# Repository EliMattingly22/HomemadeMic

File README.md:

# HomemadeMic
A simple homemade studio microphone

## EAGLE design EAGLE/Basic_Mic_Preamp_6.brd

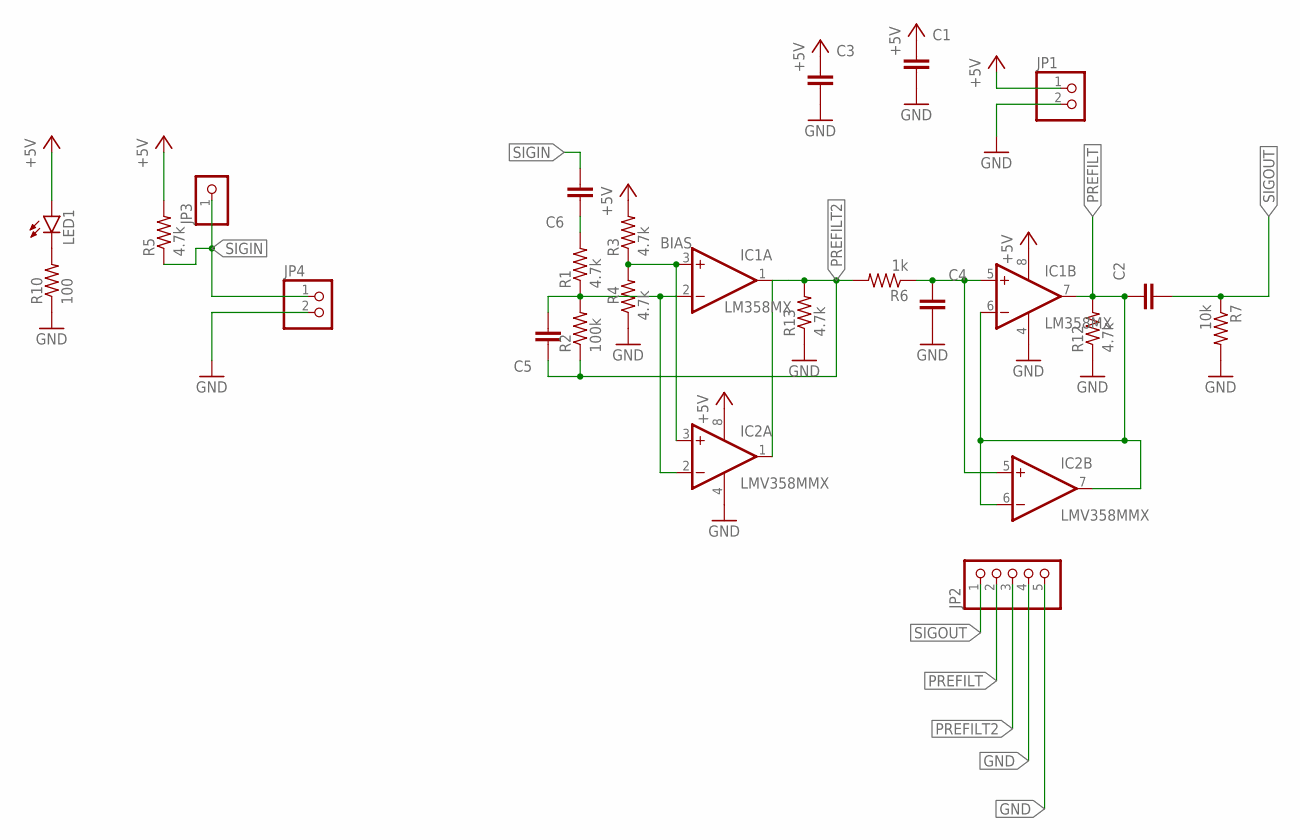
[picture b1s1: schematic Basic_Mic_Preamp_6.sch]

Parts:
C1: 10u; C1206K
C2, C6: 1u; C1206K
C3, C4: .01u; C1206K
C5: 500p; C1206K
IC1: LM358MX; SO08
IC2: LMV358MMX; MSOP08
JP1, JP4: PINHD-1X2/90; 1X02/90
JP2: PINHD-1X5/90; 1X05/90
JP3: PINHD-1X1; 1X01
LED1: LEDCHIPLED_1206; CHIPLED_1206
R1, R3, R4, R5, R12, R13: 4.7k; R1206W
R2: 100k; R1206W
R6: 1k; R1206W
R7: 10k; R1206W
R10: 100; R1206W

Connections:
+5V: C1.1, C3.1, IC1.8 (V+), IC2.8 (V+), JP1.1, LED1.A, R3.2, R5.2
BIAS: IC1.3 (+IN), IC2.3 (+IN), R3.1, R4.2
GND: C1.2, C3.2, C4.2, IC1.4 (V-), IC2.4 (V-), JP1.2, JP2.4, JP2.5, JP4.2, R4.1, R7.2, R10.1, R12.1, R13.1
unnamed: C5.2, IC1.2 (-IN), IC2.2 (-IN), R1.1, R2.2
unnamed: LED1.C, R10.2
unnamed: C6.1, R1.2
unnamed: C4.1, IC1.5 (+IN), IC2.5 (+IN), R6.1
PREFILT: C2.1, IC1.6 (-IN), IC1.7 (OUT), IC2.6 (-IN), IC2.7 (OUT), JP2.2, R12.2
PREFILT2: C5.1, IC1.1 (OUT), IC2.1 (OUT), JP2.3, R2.1, R6.2, R13.2
SIGIN: C6.2, JP3.1, JP4.1, R5.1
SIGOUT: C2.2, JP2.1, R7.1

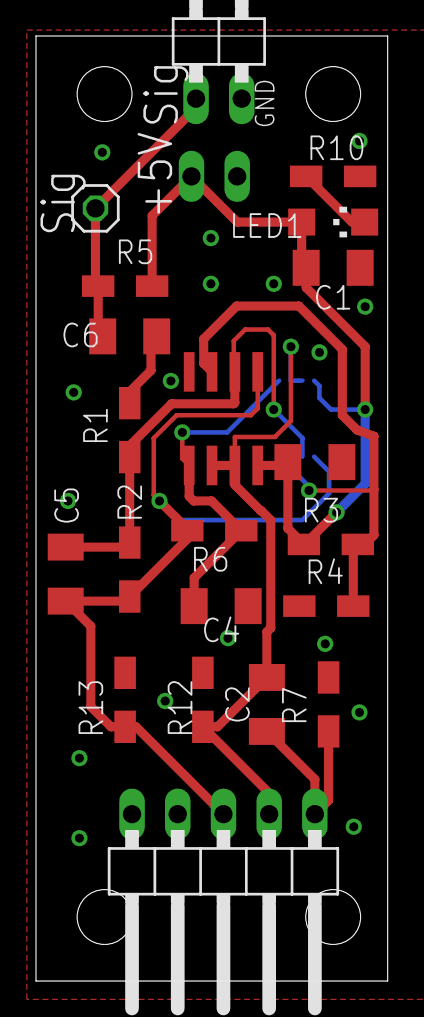
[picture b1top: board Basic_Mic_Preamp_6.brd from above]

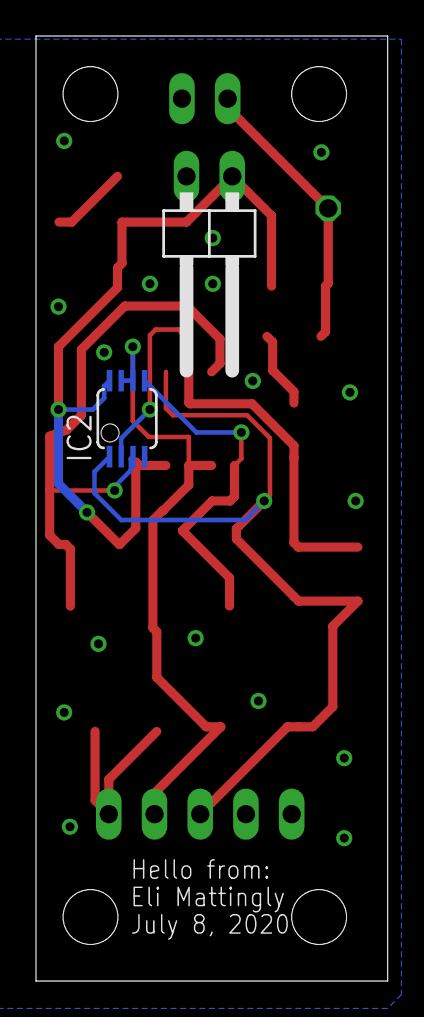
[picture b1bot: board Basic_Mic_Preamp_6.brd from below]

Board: 2 copper layers, 19.5 x 52.5 mm, 23 parts (2 on the bottom side), 11 nets.

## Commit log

2020-07-08 LT-Spice and Eagle
